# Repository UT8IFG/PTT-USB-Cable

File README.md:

# USB PTT Cable

The USB PTT Cable is a simple galvanically isolated USB-PTT interface for amateur radio equipment. It was originally designed as a USB-PTT interface for the [PA Controller](https://vhfdesign.com/pas/pa-controller.html) (manufactured by VHFDesing.com) to allow operation in digital modes. 

The basic idea is to use a plastic housing and a 4-wire cable of USB-UART converters sold on Aliexpress and other marketplaces as parts of the USB PTT Cable. This makes it easier and cheaper to build the device at home.

The USB PTT Cable is based on a CP2102 USB-UART bridge chip and its output is galvanically isolated from the USB interface by an optocoupler. It also has a two-color LED for status indication: green for standby (RX) and red for transmit (TX).

PTT is controlled by the RTS or DTR signal of the virtual COM port. The control signal can be selected by a solder jumper. By default, the RTS signal is used. 

The device's output circuit has a current limiting resistor to protect the optocoupler transistor, so the output cannot drive a large load such as a relay coil. To increase the output current, the current limiting resistor must be short-circuited with a solder jumper. In this case the optocoupler transistor will be directly connected to the output connector.

## PCB
The board is designed for hand soldering and contains 0805 size passive SMD components. The most difficult part may be soldering the CP2102 chip in the QFN-28 package.

The minimum hole diameter is 0.3mm to reduce the final production cost in some PCB factories.

The board layout allows you to make the PCB at home using the TTM (Toner Transfer Method). In this case, it will be more convenient to drill a single large hole on the ground polygon of the CP2102 chip. The board layout also has a via under the optocoupler package.

## Why CP2102?

The choice of USB-UART bridge IC for the USB PTT Cable was based on observing the behavior of the RTS and DTR signals during PC boot, PC shutdown, and IC initialization after connection to a USB port.

The following chips were tested: CH340E, PL2302HX, PL2303TA, FT323RL and CP2102. A PC was running Windows 10 and Debain Linux operating systems.

As a result, only the CP2102 chip did not have a phantom triggers on the RTS and DTR outputs during PC boot, shutdown, and connecting the bridge IC to a USB port. However, a short phantom trigger is observed during WSJT-X startup.

## Driver installation

### Linux

The CP210х driver has been distributed as part of the Linux kernel since v2.6.12. 

### Windows 10 & Windows 11

Windows 10 (version 1803 and later) and Windows 11 require manual installation of the Virtual COM Port Universal driver provided by Silicon Labs.

You can find the latest WCP210x Universal Windows Driver at this [link](https://www.silabs.com/developers/usb-to-uart-bridge-vcp-drivers?tab=downloads).

Older versions of Windows automatically install the driver through Windows Update.

### MacOS X

For computers running MacOS X 10.11 or greater, the CP210x VCP Mac OSX Driver is available [here](https://www.silabs.com/developers/usb-to-uart-bridge-vcp-drivers?tab=downloads).

### Other

Silabs also provides drivers for other operating systems such as Android or WinCE.

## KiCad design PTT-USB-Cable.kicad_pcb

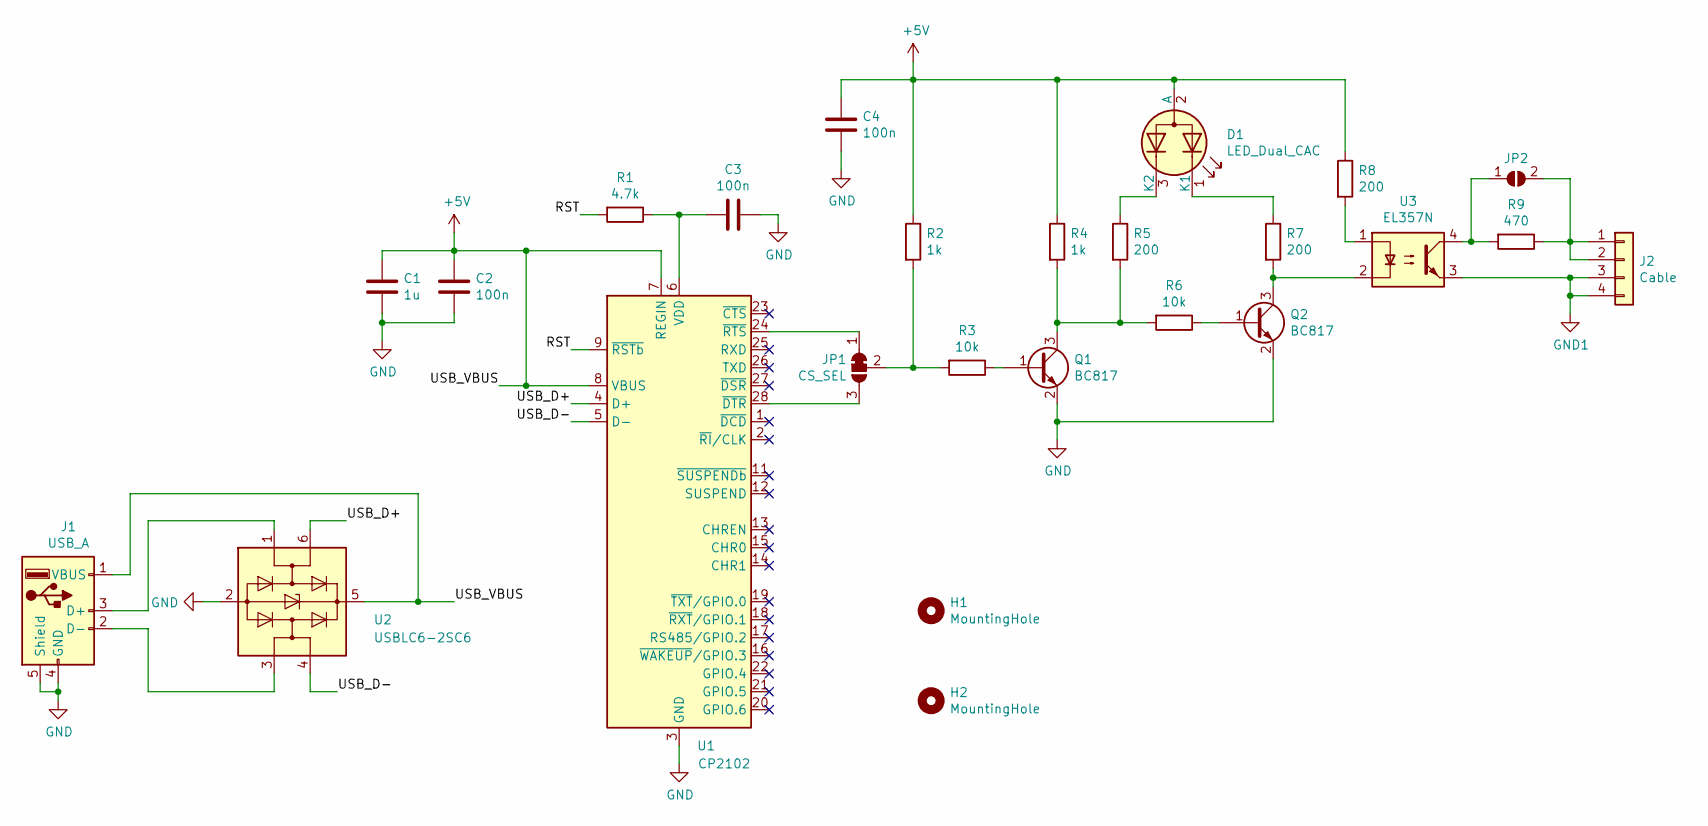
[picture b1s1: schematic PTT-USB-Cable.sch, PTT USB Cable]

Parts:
C1: 1u; C_0805_2012Metric_Pad1.18x1.45mm_HandSolder
C2, C3, C4: 100n; C_0805_2012Metric_Pad1.18x1.45mm_HandSolder
D1: LED_Dual_CAC; LED_D3.0mm-3
H1, H2: MountingHole; Hole
J1: USB_A; USB_A_CNCTech_1001-011-01101_Horizontal_TH
J2: Cable; PinHeader_1x04_P2.54mm_NoSilk
JP1: CS_SEL; SolderJumper-3_P1.3mm_Bridged12_RoundedPad1.0x1.5mm
JP2: JMP; SolderJumper-2_P1.3mm_Open_RoundedPad1.0x1.5mm
Q1, Q2: BC817; SOT-23
R1: 4.7k; R_0805_2012Metric_Pad1.20x1.40mm_HandSolder
R2, R4: 1k; R_0805_2012Metric_Pad1.20x1.40mm_HandSolder
R3, R6: 10k; R_0805_2012Metric_Pad1.20x1.40mm_HandSolder
R5, R7, R8: 200; R_0805_2012Metric_Pad1.20x1.40mm_HandSolder
R9: 470; R_0805_2012Metric_Pad1.20x1.40mm_HandSolder
U1: CP2102; QFN-28-1EP_5x5mm_P0.5mm_EP3.35x3.35mm_ThermalVias
U2: USBLC6-2SC6; SOT-23-6
U3: EL357N; SOP-4_3.8x4.1mm_P2.54mm

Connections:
+5V: C1.1, C2.1, C4.1, D1.2 (A), J1.1 (VBUS), R2.1, R4.1, R8.1, U1.7 (REGIN), U1.8 (VBUS), U2.5 (VBUS)
/RST: R1.2, U1.9 (~RSTb)
/USB_D+: U1.4 (D+), U2.6 (I/O1)
/USB_D-: U1.5 (D-), U2.4 (I/O2)
GND: C1.2, C2.2, C3.1, C4.2, J1.4 (GND), J1.5 (Shield), Q1.2 (E), Q2.2 (E), U1.3 (GND), U1.29 (GND), U2.2 (GND)
GND1: J2.3, J2.4, U3.3
unnamed: C3.2, R1.1, U1.6 (VDD)
unnamed: D1.1 (K1), R7.1
unnamed: D1.3 (K2), R5.1
unnamed: J1.2 (D-), U2.3 (I/O2)
unnamed: J1.3 (D+), U2.1 (I/O1)
unnamed: J2.1, J2.2, JP2.2 (B), R9.1
unnamed: JP1.1 (A), U1.24 (~RTS)
unnamed: JP1.2 (C), R2.2, R3.2
unnamed: JP1.3 (B), U1.28 (~DTR)
unnamed: JP2.1 (A), R9.2, U3.4
unnamed: Q1.1 (B), R3.1
unnamed: Q1.3 (C), R4.2, R5.2, R6.2
unnamed: Q2.1 (B), R6.1
unnamed: Q2.3 (C), R7.2, U3.2
unnamed: R8.2, U3.1

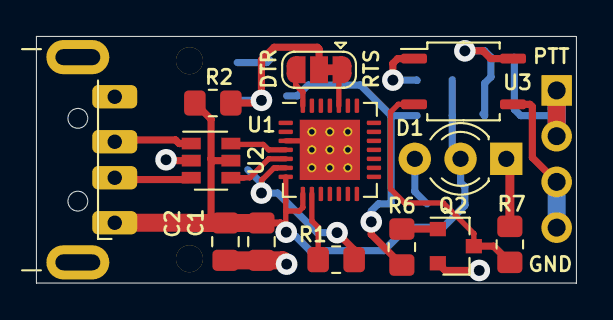
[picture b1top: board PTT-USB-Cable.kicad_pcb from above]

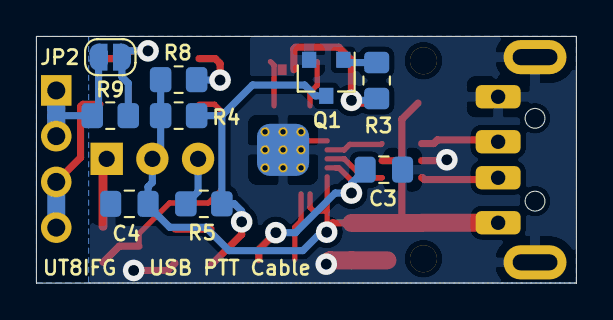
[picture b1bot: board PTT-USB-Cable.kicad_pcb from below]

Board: 2 copper layers, 30.0 x 13.7 mm, 25 parts (9 on the bottom side), 21 nets.

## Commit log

2023-08-29 Add project files
2023-09-23 Add drawing showing the location of the LED hole in the housing
2023-10-01 Add photos
2023-11-30 Add README.md
2023-12-01 Crop and resize PCB photos
